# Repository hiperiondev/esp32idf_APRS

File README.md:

<div align="center">

# esp32idf_APRS

### A complete APRS station on a single ESP32 — native ESP-IDF, no Arduino.

**IGate · Digipeater · Tracker · Weather · Telemetry**, with a built-in web admin, an on-chip AFSK/FSK soft-modem, APRS-IS uplink, a runtime sensor-driver framework and OTA firmware updates.

**🌐 Languages:** **English** · [Español](README.es.md) · [Italiano](README.it.md)

</div>

---

## What is this?

`esp32idf_APRS` turns a bare **ESP32 DevKit** plus a cheap audio interface into a complete, self-contained **APRS** station. Everything runs on the ESP32 itself — there is no Arduino core, no PlatformIO, and no external DSP library. The entire signal chain, from the correlator demodulator through DPLL bit recovery, NRZI, the HDLC framer, the AX.25 codec and Reed–Solomon FX.25 forward error correction, executes on the microcontroller using only the SAR-ADC in continuous/DMA mode, the DAC, and a general-purpose timer.

In one sentence, the firmware **demodulates** AFSK/FSK audio from a radio's speaker or discriminator output, **decodes** HDLC/AX.25 (optionally FX.25 error-corrected) frames, **gates** them to APRS-IS over Wi-Fi, **digipeats** them back on RF, **beacons** its own position, weather and telemetry, **modulates** and transmits frames back through the ESP32's 8-bit DAC — and is configured entirely through a web admin served by the device itself. No serial console, no recompilation for ordinary settings.

> 📖 **The full, exhaustive documentation lives at [esp32idf-aprs.readthedocs.io](https://esp32idf-aprs.readthedocs.io/)** — trilingual (English / Español / Italiano), with getting-started guides, hardware wiring, the DSP signal chain, the configuration engine, HTTP routes and troubleshooting. **This README is only a presentation. For anything beyond a first look, go to the docs.**

---

## Highlights

- **On-chip soft-modem.** AFSK 1200 Bd Bell 202 (standard APRS) with up to twelve parallel demodulators (a multi-slicer set on four tilted prefilters covering about 33 dB of tone twist, from discriminator and speaker audio alike, tunable from the web admin, with a tone-band receive level meter), plus AFSK 1200 Bd V.23, AFSK 300 Bd, and **G3RUH 9600 Bd FSK** — all in pure C on the ESP32's own ADC/DAC.
- **FX.25 forward error correction.** Reed–Solomon FEC over AX.25, RX-only or RX+TX, for reliable decodes in weak-signal conditions.
- **Full APRS-IS IGate.** Bidirectional **RF→INET** and **INET→RF** gating with duplicate suppression, `qAR`/`qAO` construction, payload-type gating, callsign budlists, a local range gate (haversine distance), a prefix whitelist and, on the INET→RF side, a position requirement, a locally-heard source test and per-source spacing that keep a wide APRS-IS subscription off the local channel. Up to four APRS-IS servers can be listed, with automatic failover between the enabled ones.
- **BrandMeister APRS interconnect.** Recognises, gates and routes the APRS traffic BrandMeister injects, over the APRS-IS session the IGate already has — an `APBMxx` tocall, a `DMR` path alias or a named entry gateway identifies it. Its own page, off by default. **No DMR connection of any kind is involved.**
- **Digipeater.** A four-row n-N alias table (WIDE1-1 / WIDE2-2 / WIDE#-2 by default), each row with its own hop limit and trace/flood mode, plus hop-count trapping, fill-in-only operation and duplicate suppression.
- **Beacons, messaging & chat.** Fixed-position beacons for tracker/igate/digi, APRS text messaging with ack/retry (RF and/or INET), and an in-browser message chat UI.
- **GNSS receiver & live tracking.** An NMEA module on its own UART (RMC/GGA/GSA/GSV/VTG, multi-constellation) with a master switch, a live view page refreshed once a second, and a *Use GPS* control that fills any page's position fields from the current fix. The Tracker beacon can transmit the live fix instead of a fixed position, with SmartBeaconing making the interval speed-adaptive and pegging it on corners.
- **APRS query responder.** Answers the general `?APRS?`/`?WX?`/`?IGATE?`/`?QRU?` queries and the directed set (`?APRSD`/`?APRSH`/`?APRSM`/`?APRSO`/`?APRSP`/`?APRSS`/`?APRST`/`?PING?`), each with per-type and per-source rate limits, plus an optional periodic station-capabilities beacon.
- **Weather & telemetry.** On-air APRS Weather Reports with 1 Hz sensor refresh and per-field averaging, plus APRS Telemetry (analog A1–A5 + digital B1–B8) with `T#nnn` reports and metadata.
- **Winlink radio e-mail (APRSLink).** The station reads and writes its own `CALLSIGN@winlink.org` mail through the `WLNK-1` service — challenge/response login with the password never on the air, a paced one-command-at-a-time session, and a browser terminal whose mailbox listing carries per-message read/reply/forward/delete buttons — and, separately, relays a neighbouring RF station's own Winlink session through its IGate.
- **Objects, items & bulletins.** Up to five own-station APRS Objects/Items and five bulletins (BLN1–BLN5), each on RF and/or INET with expiry/decay control.
- **Telegram bot.** An optional bot alongside the APRS services — long polling, per-user and per-chat authorization, station-message and bulletin routing to Telegram, and a Mini App button — so the station can be checked on and lightly controlled from a phone.
- **Runtime sensor framework.** A dynamic, self-registering driver registry (`sensors_local`) — includes a BME280/BMP280 (I²C) driver out of the box, plus an optional BMP180 one on the same bus.
- **Web admin, 22 pages.** HTTP Basic auth with two accounts — an administrator and an optional read-only one that sees every page, changes nothing, and may only start and stop the console log viewer —, a live dashboard with a live traffic log (JSON long-poll) and a last-heard JSON feed, LittleFS file management (upload/download/delete/format), Wi-Fi AP/STA/AP+STA with scan and TX-power control, CPU frequency control (80/160/240 MHz), and an on-demand console log viewer that mirrors the serial output into the browser. The whole UI is responsive from one stylesheet — on a tablet or a phone the sidebar becomes a slide-in drawer, form rows collapse to a single column, wide tables scroll within the page and the controls grow to a touch size.
- **OTA updates with auto-rollback.** Dual `ota_0`/`ota_1` app slots; a failed image rolls back automatically on the next boot.
- **Trilingual UI.** English, Spanish and Italian (compile-time, one language per image).

---

## Feature matrix

| Area | Notes |
|---|---|
| AFSK 1200 Bd Bell 202 | Up to twelve parallel demodulators, default profile |
| AFSK 1200 Bd V.23 · AFSK 300 Bd · G3RUH 9600 Bd FSK | Multiple selectable modem profiles |
| HDLC / AX.25 UI frame RX + TX | Full soft-modem TX/RX path |
| FX.25 (Reed–Solomon FEC over AX.25) | RX-only / RX+TX modes |
| PTT keying | Compile-time GPIO + polarity, minimum-unkey hold |
| CSMA / TX time-slot / TXDelay preamble / TXTail | `preamble`, `tx_tail` (TXTail, default 20 ms), `tx_timeslot`, `csma_persist`, `csma_slot_ms` (SlotTime), `csma_busy_max_s` (busy-channel wait, 0 = unlimited) |
| Transmit duty-cycle limiter | Optional ceiling over a rolling 10-minute window |
| APRS-IS IGate RF→INET & INET→RF | Filters, dedup, budlist, third-party unwrap opt-in, INET→RF flood gates |
| APRS-IS multiserver failover | 4 server slots, circular retry over the enabled ones |
| Local range gate & prefix gate | Haversine distance + callsign-prefix whitelist |
| BrandMeister APRS interconnect | Recognition, gating and message routing over the existing APRS-IS session; no DMR link |
| Digipeater | Configurable n-N alias table (trace/flood), hop trapping, dup-suppression |
| Objects / Items · Bulletins | Up to 5 each, RF and/or INET, expiry/decay |
| Telegram bot | Long polling, per-user/chat authorization, message & bulletin routing, Mini App button |
| Messaging + ack/retry · Chat UI | RF and/or INET |
| Winlink radio e-mail (APRSLink) | Own mailbox over `WLNK-1`, plus gateway for local stations |
| GNSS receiver (NMEA, own UART) | Master switch, live view page, *Use GPS* position fill on every page |
| Live GPS tracking + SmartBeaconing | Tracker beacon only; speed-adaptive interval and corner-pegging |
| APRS query responder | General `?APRS?`/`?WX?`/`?IGATE?`/`?QRU?` + directed set, rate-limited; capabilities beacon |
| Weather Report | 1 Hz sensor refresh, optional averaging |
| Telemetry | Analog A1–A5 + digital B1–B8, `T#nnn` + metadata |
| Sensor driver framework | Dynamic registry, BME280/BMP280 driver included |
| Web admin | 22 pages, live dashboard, live traffic log + last-heard feed, console log viewer, per-option contextual help |
| Storage | LittleFS 512 KB, upload/download/delete/format |
| Networking | Wi-Fi AP/STA/AP+STA, scan, TX power, SNTP (UTC clock, selectable timezone for display) |
| CPU frequency control | 80 / 160 / 240 MHz |
| OTA update | `ota_0`/`ota_1` slots, auto-rollback |
| Localization | EN / ES / IT, compile-time, labels and help balloons alike |

---

## Hardware

- **Target:** ESP32 (classic, Xtensa dual-core), 4 MB flash. Dual-core is **required** — the ADC ISR and DAC sample clock are pinned to different cores on purpose.
- **Audio in (ADC):** default `GPIO33` (ADC1). **GPIO 32–39 only** — ADC2 is unusable while Wi-Fi is up.
- **Audio out (DAC):** default `GPIO25`. **GPIO 25 or 26 only** — the ESP32 DAC is hard-wired to those pads.
- **PTT:** default `GPIO26`, polarity selectable at compile time.
- **GNSS (optional):** UART2, default `GPIO16` (RX, from the module's TX) and `GPIO17` (TX). Set in `main/include/gps.h`. **Unusable on an ESP32-WROVER**, where those pins belong to the SPI PSRAM die.
- **Note:** ESP32-S3/C3/C6/H2 have **no DAC** and cannot run the TX path unmodified.

Board wiring (audio pins, PTT pin/polarity, ADC sample rate) is set as compile-time constants in the top-level `CMakeLists.txt`. A KiCad radio-interface schematic is included under `schematics/`.

The audio interface itself can be as small as one coupling capacitor and one level trimmer per direction: the Radiomodem page carries an **Audio interface** section that biases the ADC input from the pad's own pull resistors, sets the transmit output swing and sample rate, warns on receive over-range and bounds how long the transmitter may stay keyed. Every one of those settings defaults to the behaviour an interface board with its own bias network, attenuators and reconstruction filter expects, so an existing build is unaffected. Two buttons next to LOOP TEST — **RX LEVEL** and **TX TEST** — set the two trimmers once a transceiver has replaced the loopback jumper.

> Full pinout tables and wiring constraints are in the [Hardware chapter of the documentation](https://esp32idf-aprs.readthedocs.io/en/latest/en/hardware.html).

---

## Quick start

```bash
# Requires ESP-IDF v6.1 (tested and locked at 6.1)
idf.py set-target esp32
idf.py build
idf.py -p PORT flash monitor
```

On first boot the device brings up a Wi-Fi AP; connect and open the web admin to configure your callsign, radio and services. After the one-time USB/UART flash, all further updates can be done from the web admin's **About / Firmware** page over OTA.

> 📖 The step-by-step first-run guide is in [Getting Started](https://esp32idf-aprs.readthedocs.io/en/latest/en/getting-started.html).

---

## Documentation

**Everything is documented in full at 👉 [esp32idf-aprs.readthedocs.io](https://esp32idf-aprs.readthedocs.io/)**

The documentation is trilingual and organised into *Functionalities* (what the station does), *Capabilities* (cross-cutting properties), *Internals* (how it is built) and a *Reference* section:

- 🇬🇧 [English](https://esp32idf-aprs.readthedocs.io/en/latest/en/index.html)
- 🇪🇸 [Español](https://esp32idf-aprs.readthedocs.io/en/latest/es/index.html)
- 🇮🇹 [Italiano](https://esp32idf-aprs.readthedocs.io/en/latest/it/index.html)

This README is a presentation only — **please consult the documentation for installation, wiring, configuration and internals.**

---

## Credits & license

Created by **Emiliano Augusto González (LU3VEA)**.

Built on ideas from earlier projects — [VP-Digi](https://github.com/sq8vps/vp-digi), [ESP32APRS](https://github.com/nakhonthai/ESP32APRS_Audio) and [LibAPRS](https://github.com/markqvist/LibAPRS); please refer to their authors for more information.

Released under the **GNU General Public License v3**. See [LICENSE](LICENSE).

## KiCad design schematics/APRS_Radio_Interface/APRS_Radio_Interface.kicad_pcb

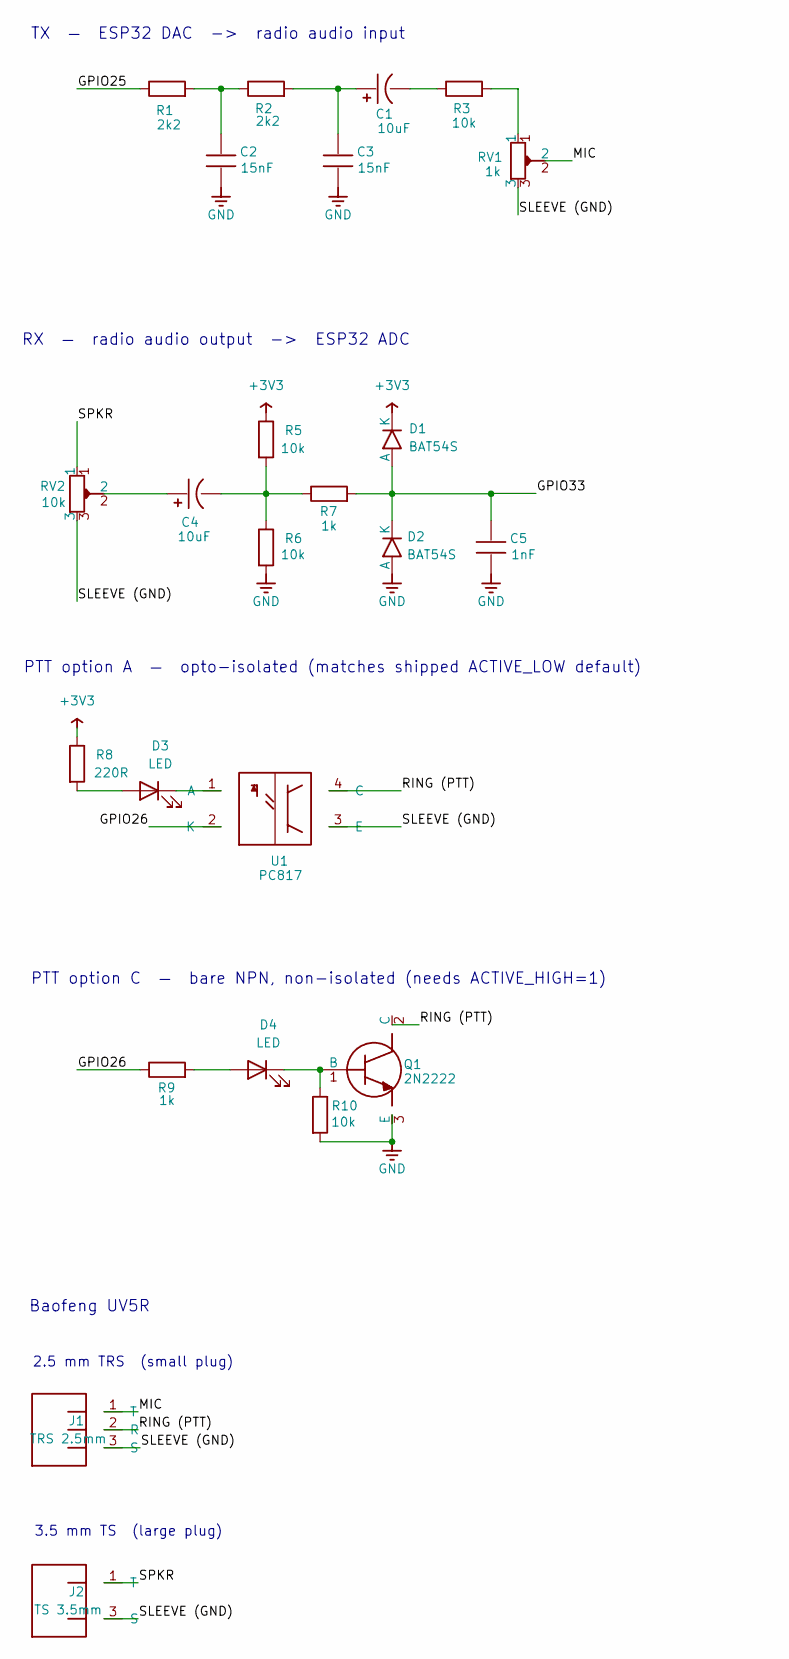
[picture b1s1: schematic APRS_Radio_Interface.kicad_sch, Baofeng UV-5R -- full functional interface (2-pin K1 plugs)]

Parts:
C1, C4: 10uF
C2, C3: 15nF
C5: 1nF
D1, D2: BAT54S
D3, D4: LED
J1: TRS 2.5mm
J2: TS 3.5mm
Q1: 2N2222
R1, R2: 2k2
R3, R5, R6, R10: 10k
R7, R9: 1k
R8: 220R
RV1: 1k
RV2: 10k
U1: PC817

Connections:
+3V3: D1.1 (K), R5.1, R8.1; also elsewhere on the board
GND: C2.2, C3.2, C5.2, D2.2 (A), Q1.3 (E), R6.2, R10.2; also elsewhere on the board
GPIO25: R1.1; also elsewhere on the board
GPIO26: R9.1, U1.2 (K); also elsewhere on the board
GPIO33: C5.1, D1.2 (A), D2.1 (K), R7.2; also elsewhere on the board
MIC: J1.1 (T), RV1.2
unnamed: C4.1, RV2.2
unnamed: C1.2, R3.1
unnamed: R3.2, RV1.1
unnamed: D4.1 (K), Q1.1 (B), R10.1
unnamed: D4.2 (A), R9.2
unnamed: C4.2, R5.2, R6.1, R7.1
unnamed: D3.1 (K), U1.1 (A)
unnamed: D3.2 (A), R8.2
unnamed: C2.1, R1.2, R2.1
unnamed: C1.1, C3.1, R2.2
RING (PTT): J1.2 (R), Q1.2 (C), U1.4 (C)
SLEEVE (GND): J1.3 (S), J2.3 (S), RV1.3, RV2.3, U1.3 (E)
SPKR: J2.1 (T), RV2.1

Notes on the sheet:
3.5 mm TS (large plug)
TX — ESP32 DAC -> radio audio input
2.5 mm TRS (small plug)
Baofeng UV5R
RX — radio audio output -> ESP32 ADC
PTT option A — opto-isolated (matches shipped ACTIVE_LOW default)
PTT option C — bare NPN, non-isolated (needs ACTIVE_HIGH=1)

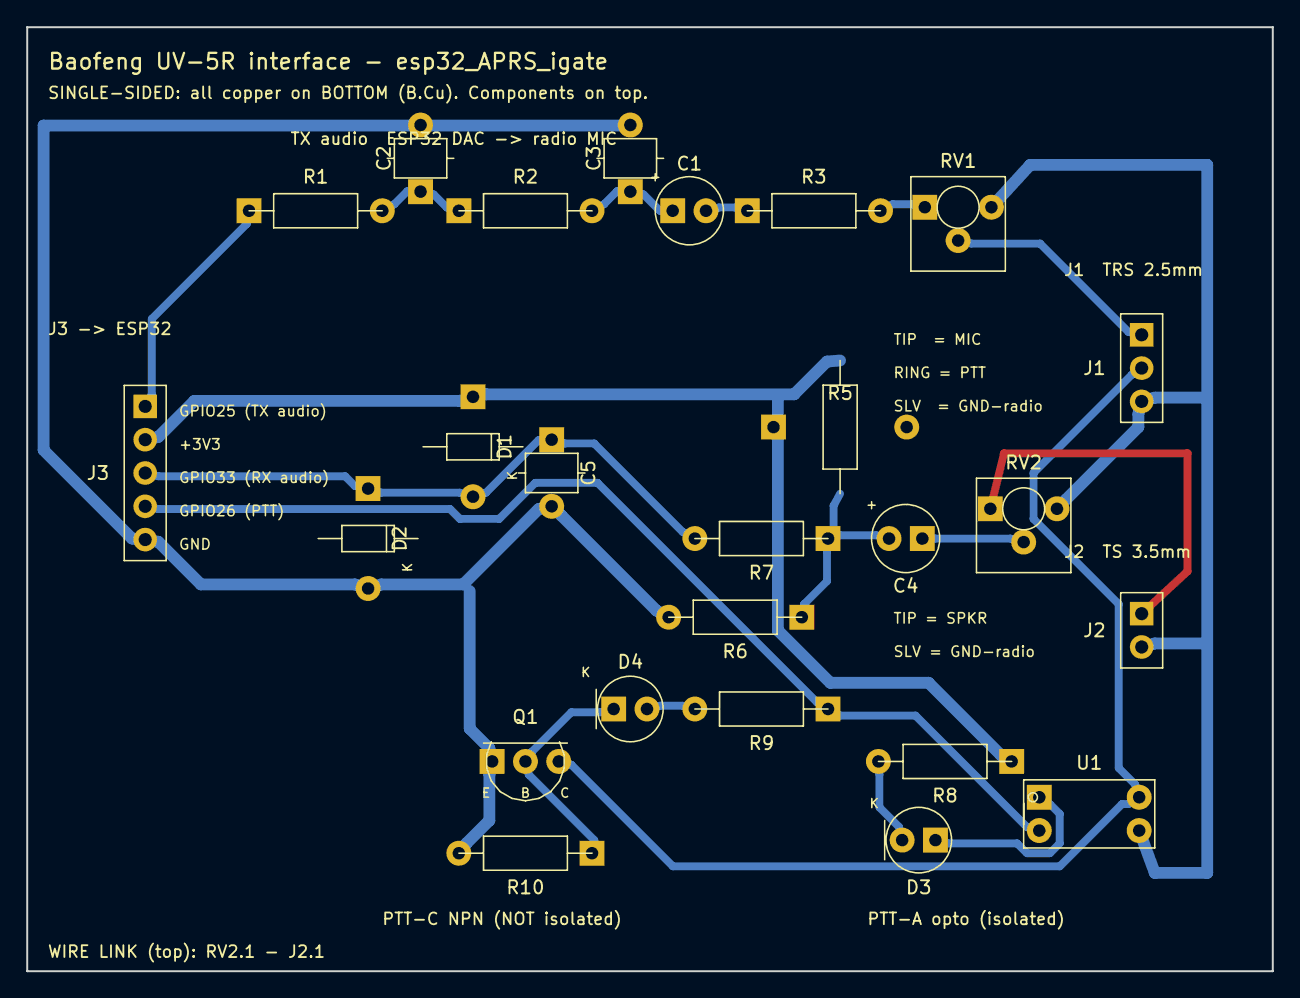
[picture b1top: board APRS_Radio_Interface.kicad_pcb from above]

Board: 2 copper layers, 95.0 x 72.0 mm, 25 parts (0 on the bottom side), 19 nets.

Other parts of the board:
J3: ESP32; HDR_1x05

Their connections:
+3V3: J3.2; also elsewhere on the board
GND: J3.5; also elsewhere on the board
GPIO25: J3.1; also elsewhere on the board
GPIO26: J3.4; also elsewhere on the board
GPIO33: J3.3; also elsewhere on the board

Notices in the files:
README.md:
License: GPLv3
